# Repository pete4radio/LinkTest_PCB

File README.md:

# LinkTest_PCB
PCB for Dual LinkTesting

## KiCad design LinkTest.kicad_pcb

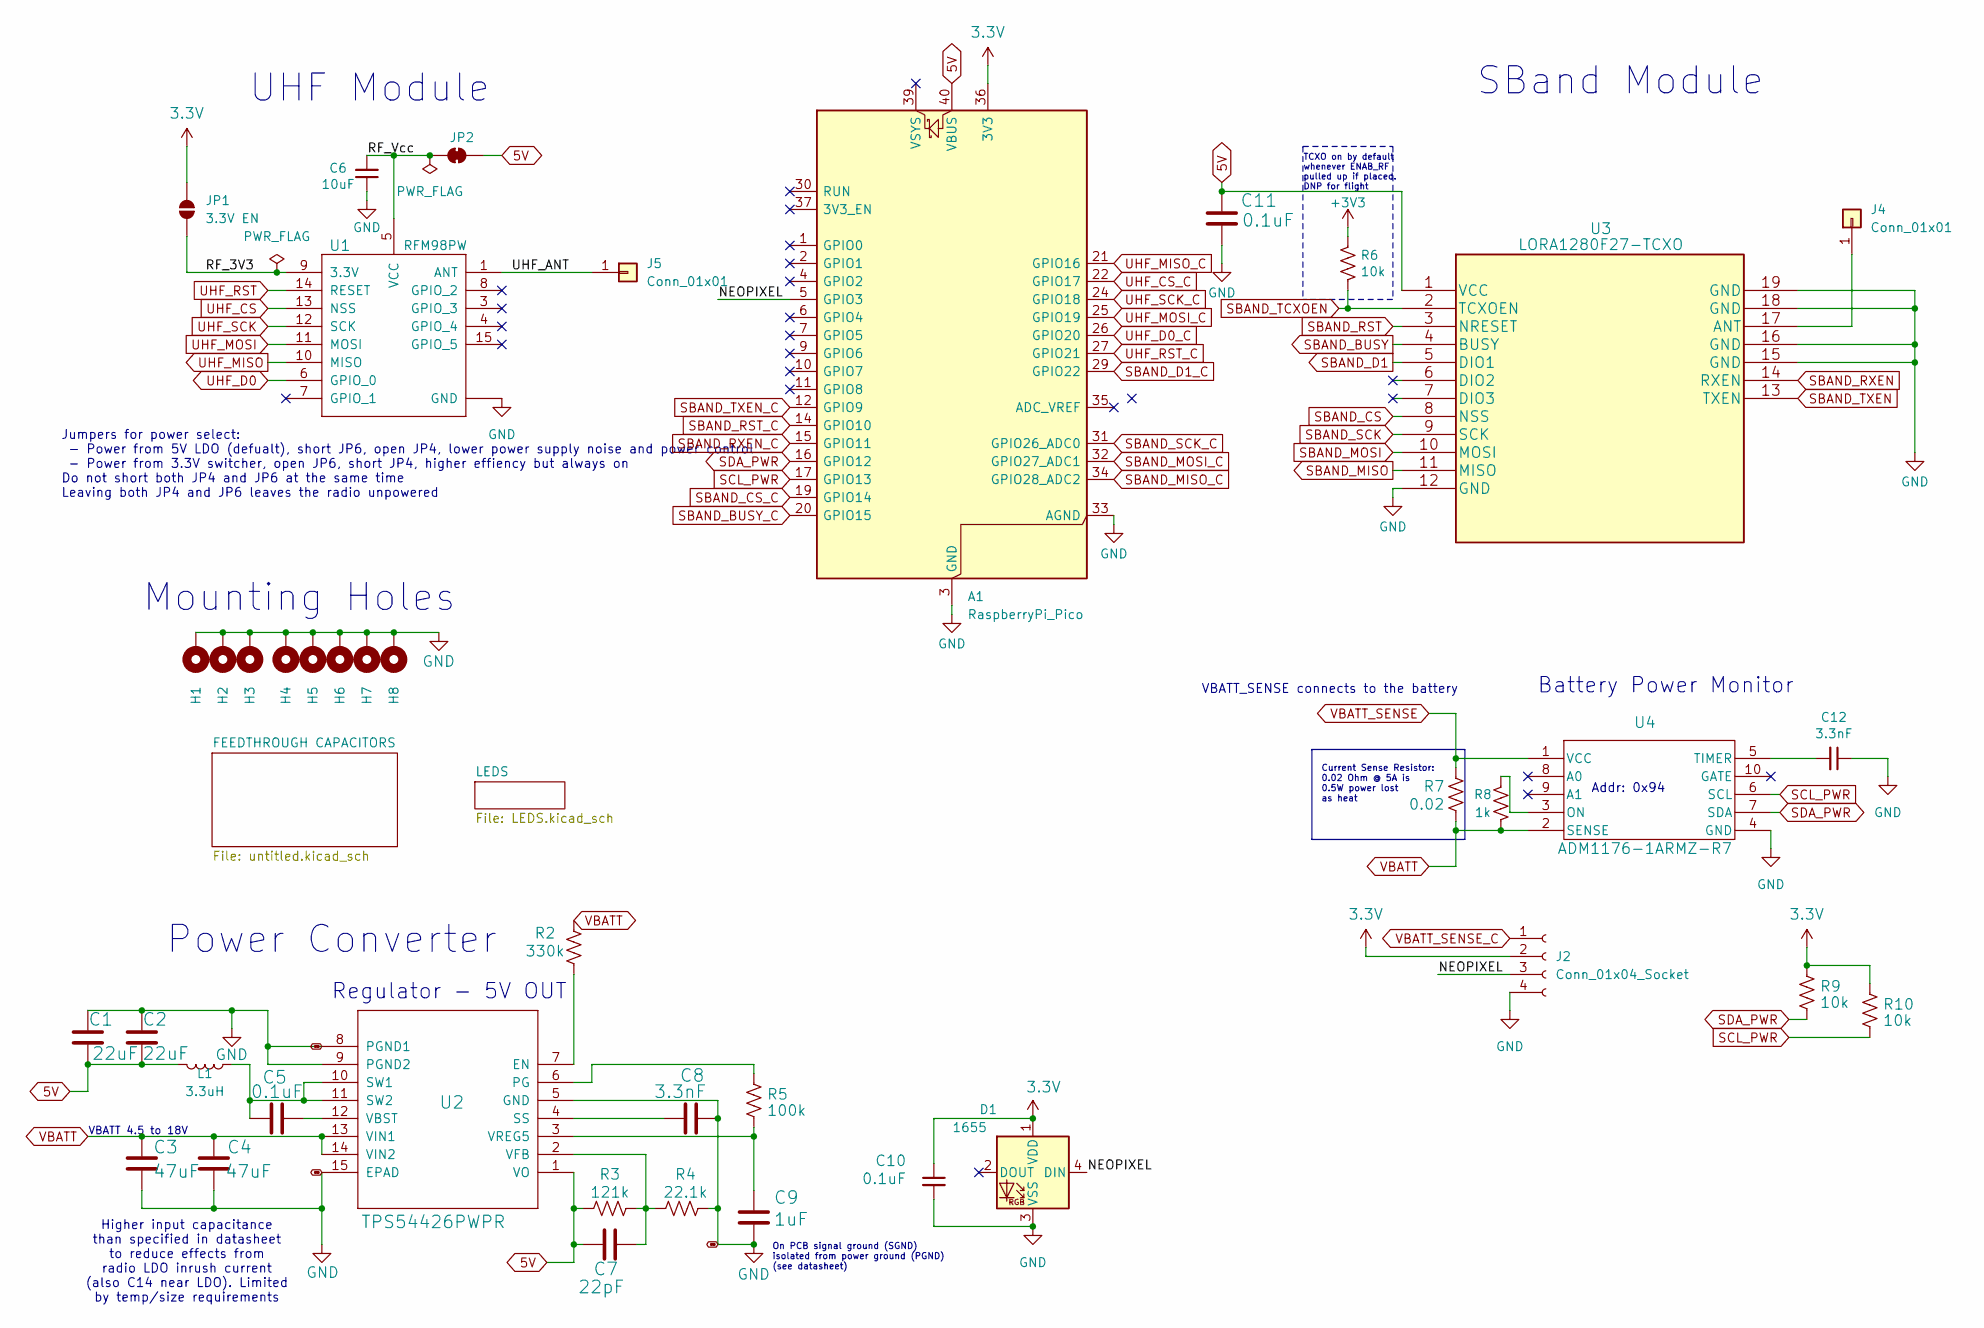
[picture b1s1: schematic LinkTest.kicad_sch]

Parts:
A1: RaspberryPi_Pico; RaspberryPi_Pico_SMD
C1, C2: 22uF; C_0603_1608Metric
C3, C4: 47uF; C_1210_3225Metric
C5, C10, C11: 0.1uF; C_0603_1608Metric
C6: 10uF; C_0603_1608Metric
C7: 22pF; C_0603_1608Metric
C8, C12: 3.3nF; C_0603_1608Metric
C9: 1uF; C_0603_1608Metric
D1: 1655; LED_WS2812B_PLCC4_5.0x5.0mm_P3.2mm; Manufacturer_Part_Number SK6812
H1, H2, H3, H4, H5, H6, H7, H8: MountingHole_Pad; MountingHole_2.7mm_M2.5_DIN965_Pad
J2: Conn_01x04_Socket; PinHeader_1x04_P2.54mm_Vertical
J4, J5: Conn_01x01; TestPoint_Keystone_5019_Miniature
JP1: 3.3V EN; SolderJumper-2_P1.3mm_Open_RoundedPad1.0x1.5mm
JP2: Jumper_3_Bridged12; SolderJumper-2_P1.3mm_Bridged_RoundedPad1.0x1.5mm
L1: 3.3uH; L_2141; Manufacturer_Part_Number HPC5040NF-3R3MTH
R2: 330k; R_0603_1608Metric
R3: 121k; R_0603_1608Metric
R4: 22.1k; R_0603_1608Metric
R5: 100k; R_0603_1608Metric
R6, R9, R10: 10k; R_0603_1608Metric
R7: 0.02; R_2512_6332Metric
R8: 1k; R_0603_1608Metric
U1: RFM98PW; Manufacturer_Part_Number RFM98PW
U2: TPS54426PWPR; PWP14_2P31X2P46-L; Manufacturer_Part_Number TPS54226PWPR
U3: LORA1280F27-TCXO; LORA128XF27
U4: ADM1176-1ARMZ-R7; Manufacturer_Part_Number ADM1176-1ARMZ-R7

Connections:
3.3V: A1.36 (3V3), C10.1, D1.1 (VDD), J2.2, JP1.2 (B), R9.1, R10.1
5V: A1.40 (VBUS), C1.2, C2.2, C7.1, C11.1, JP2.1 (A), L1.2, R3.2, U2.1 (VO), U3.1 (VCC)
+3V3: R6.1
/NEOPIXEL: A1.5 (GPIO3), D1.4 (DIN), J2.3
/RF_3V3: JP1.1 (A), U1.9 (3.3V)
/RF_Vcc: C6.2, JP2.2 (B), U1.5 (VCC)
/UHF_ANT: J5.1, U1.1 (ANT)
GND: A1.3 (GND), A1.8 (GND), A1.13 (GND), A1.18 (GND), A1.23 (GND), A1.28 (GND), A1.33 (AGND), A1.38 (GND), C1.1, C2.1, C3.2, C4.2, C6.1, C8.2, C9.2, C10.2, C11.2, C12.1, D1.3 (VSS), H1.1, H2.1, H3.1, H4.1, H5.1, H6.1, H7.1, H8.1, J2.4, R4.1, U1.2 (GND), U1.16 (GND), U1.17 (GND), U2.5 (GND), U2.8 (PGND1), U2.9 (PGND2), U2.15 (EPAD), U3.12 (GND), U3.15 (GND), U3.16 (GND), U3.18 (GND), U3.19 (GND), U4.4 (GND); also elsewhere on the board
unnamed: J4.1, U3.17 (ANT)
unnamed: R2.2, U2.7 (EN)
unnamed: R5.1, U2.6 (PG)
unnamed: C8.1, U2.4 (SS)
unnamed: C5.1, L1.1, U2.10 (SW1), U2.11 (SW2)
unnamed: C5.2, U2.12 (VBST)
unnamed: C7.2, R3.1, R4.2, U2.2 (VFB)
unnamed: C9.1, R5.2, U2.3 (VREG5)
unnamed: R8.2, U4.3 (ON)
unnamed: C12.2, U4.5 (TIMER)
SBAND_BUSY: U3.4 (BUSY); also elsewhere on the board
SBAND_BUSY_C: A1.20 (GPIO15); also elsewhere on the board
SBAND_CS: U3.8 (NSS); also elsewhere on the board
SBAND_CS_C: A1.19 (GPIO14); also elsewhere on the board
SBAND_D1: U3.5 (DIO1); also elsewhere on the board
SBAND_D1_C: A1.29 (GPIO22); also elsewhere on the board
SBAND_MISO: U3.11 (MISO); also elsewhere on the board
SBAND_MISO_C: A1.34 (GPIO28_ADC2); also elsewhere on the board
SBAND_MOSI: U3.10 (MOSI); also elsewhere on the board
SBAND_MOSI_C: A1.32 (GPIO27_ADC1); also elsewhere on the board
SBAND_RST: U3.3 (NRESET); also elsewhere on the board
SBAND_RST_C: A1.14 (GPIO10); also elsewhere on the board
SBAND_RXEN: U3.14 (RXEN); also elsewhere on the board
SBAND_RXEN_C: A1.15 (GPIO11); also elsewhere on the board
SBAND_SCK: U3.9 (SCK); also elsewhere on the board
SBAND_SCK_C: A1.31 (GPIO26_ADC0); also elsewhere on the board
SBAND_TCXOEN: R6.2, U3.2 (TCXOEN)
SBAND_TXEN: U3.13 (TXEN); also elsewhere on the board
SBAND_TXEN_C: A1.12 (GPIO9); also elsewhere on the board
SCL_PWR: A1.17 (GPIO13), R10.2, U4.6 (SCL)
SDA_PWR: A1.16 (GPIO12), R9.2, U4.7 (SDA)
UHF_CS: U1.13 (NSS); also elsewhere on the board
UHF_CS_C: A1.22 (GPIO17); also elsewhere on the board
UHF_D0: U1.6 (GPIO_0); also elsewhere on the board
UHF_D0_C: A1.26 (GPIO20); also elsewhere on the board
UHF_MISO: U1.10 (MISO); also elsewhere on the board
UHF_MISO_C: A1.21 (GPIO16); also elsewhere on the board
UHF_MOSI: U1.11 (MOSI); also elsewhere on the board
UHF_MOSI_C: A1.25 (GPIO19); also elsewhere on the board
UHF_RST: U1.14 (RESET); also elsewhere on the board
UHF_RST_C: A1.27 (GPIO21); also elsewhere on the board
UHF_SCK: U1.12 (SCK); also elsewhere on the board
UHF_SCK_C: A1.24 (GPIO18); also elsewhere on the board
VBATT: C3.1, C4.1, R2.1, R7.1, R8.1, U2.13 (VIN1), U2.14 (VIN2), U4.2 (SENSE); also elsewhere on the board
VBATT_SENSE: R7.2, U4.1 (VCC); also elsewhere on the board
VBATT_SENSE_C: J2.1; also elsewhere on the board

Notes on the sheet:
SBand Module
Addr: 0x94
Power Converter
VBATT 4.5 to 18V
Current Sense Resistor: 0.02 Ohm @ 5A is 0.5W power lost as heat
On PCB signal ground (SGND) isolated from power ground (PGND) (see datasheet)
UHF Module
VBATT_SENSE connects to the battery
Regulator - 5V OUT
Higher input capacitance than specified in datasheet to reduce effects from radio LDO inrush current (also C14 near LDO). Limited by temp/size requirements
Battery Power Monitor
Jumpers for power select: - Power from 5V LDO (defualt), short JP6, open JP4, lower power supply noise and power control - Power from 3.3V switcher, open JP6, short JP4, higher effiency but always on Do not short both JP4 and JP6 at the same time Leaving both JP4 and JP6 leaves the radio unpowered
Mounting Holes
TCXO on by default whenever ENAB_RF pulled up if placed. DNP for flight

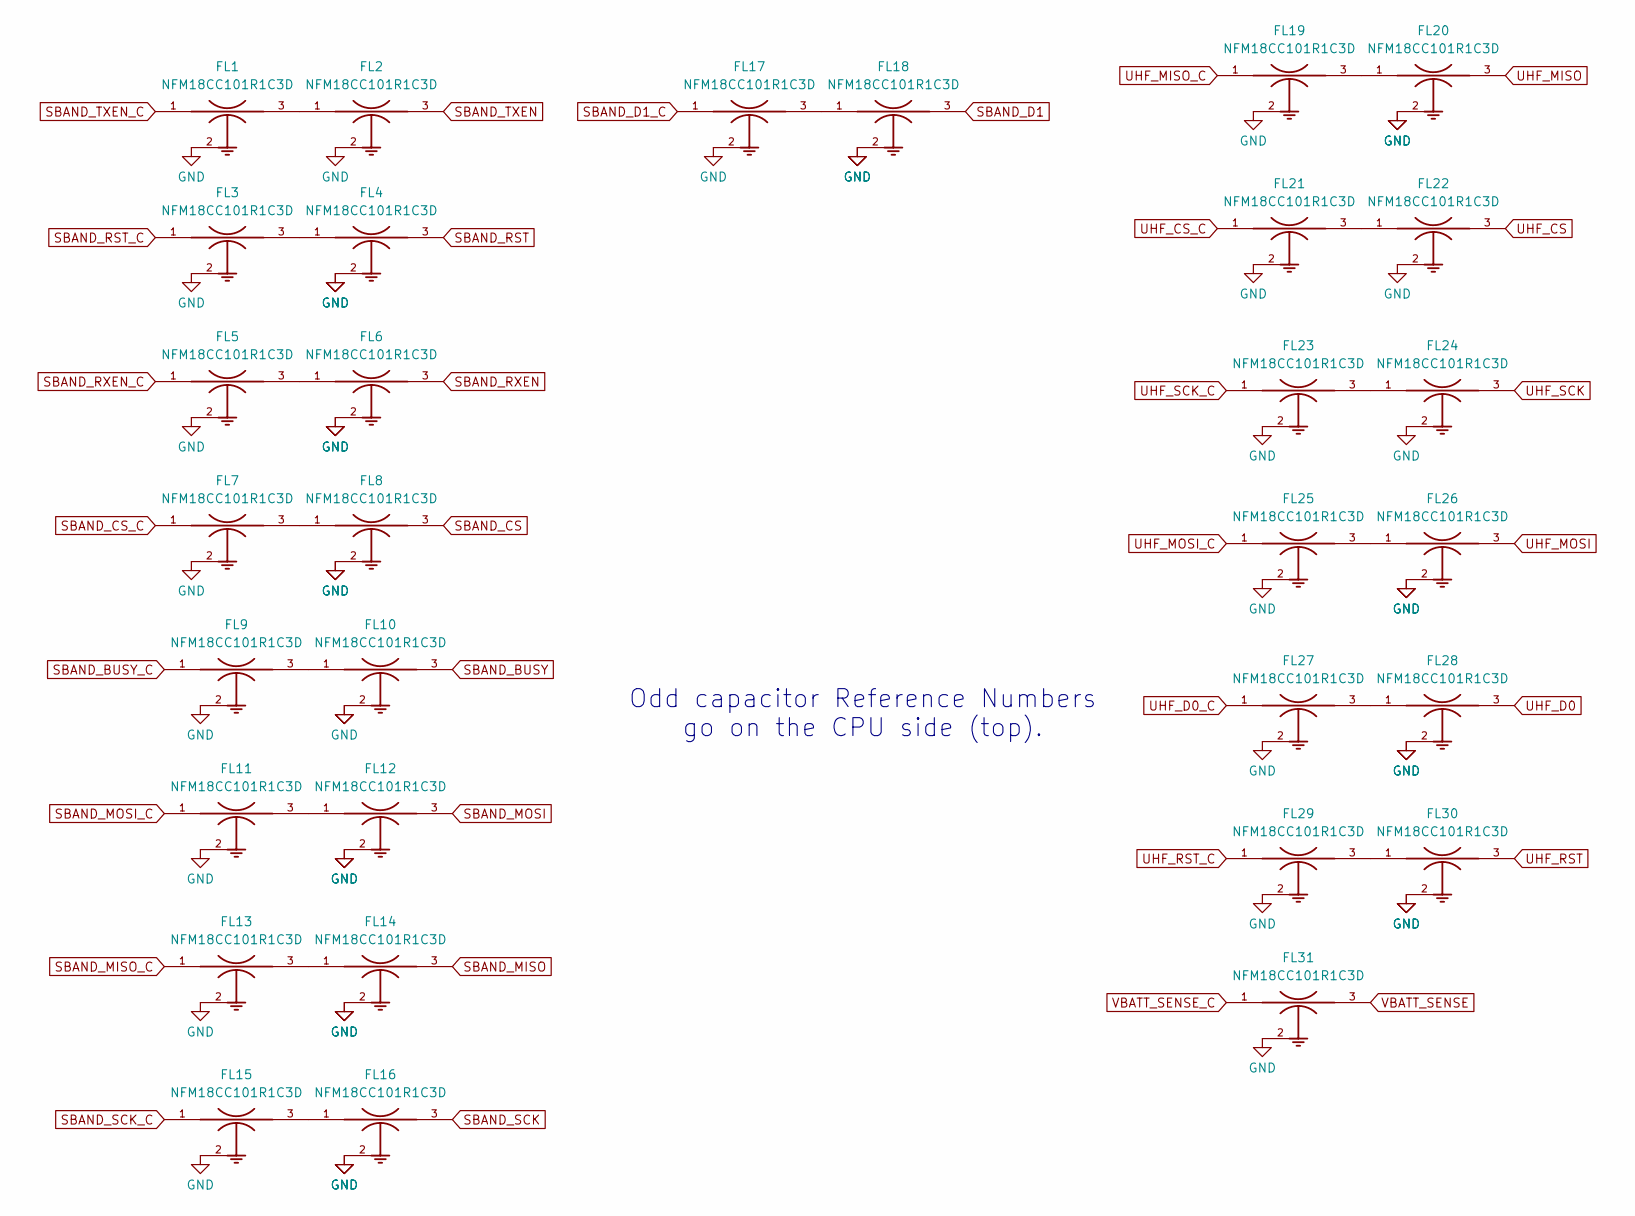
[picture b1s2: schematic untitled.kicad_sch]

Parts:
FL1, FL2, FL3, FL4, FL5, FL6, FL7, FL8, FL9, FL10, FL11, FL12, FL13, FL14, FL15, FL16, FL17, FL18, FL19, FL20, FL21, FL22, FL23, FL24, FL25, FL26, FL27, FL28, FL29, FL30, FL31: NFM18CC101R1C3D; FIL_NFM18CC101R1C3D; DigiKey_Part_Number 490-6961-1-ND

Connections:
GND: FL1.2, FL1.2_1, FL1.2_2, FL1.2_3, FL1.2_4, FL2.2, FL2.2_1, FL2.2_2, FL2.2_3, FL2.2_4, FL3.2, FL3.2_1, FL3.2_2, FL3.2_3, FL3.2_4, FL4.2, FL4.2_1, FL4.2_2, FL4.2_3, FL4.2_4, FL5.2, FL5.2_1, FL5.2_2, FL5.2_3, FL5.2_4, FL6.2, FL6.2_1, FL6.2_2, FL6.2_3, FL6.2_4, FL7.2, FL7.2_1, FL7.2_2, FL7.2_3, FL7.2_4, FL8.2, FL8.2_1, FL8.2_2, FL8.2_3, FL8.2_4, FL9.2, FL9.2_1, FL9.2_2, FL9.2_3, FL9.2_4, FL10.2, FL10.2_1, FL10.2_2, FL10.2_3, FL10.2_4, FL11.2, FL11.2_1, FL11.2_2, FL11.2_3, FL11.2_4, FL12.2, FL12.2_1, FL12.2_2, FL12.2_3, FL12.2_4, FL13.2, FL13.2_1, FL13.2_2, FL13.2_3, FL13.2_4, FL14.2, FL14.2_1, FL14.2_2, FL14.2_3, FL14.2_4, FL15.2, FL15.2_1, FL15.2_2, FL15.2_3, FL15.2_4, FL16.2, FL16.2_1, FL16.2_2, FL16.2_3, FL16.2_4, FL17.2, FL17.2_1, FL17.2_2, FL17.2_3, FL17.2_4, FL18.2, FL18.2_1, FL18.2_2, FL18.2_3, FL18.2_4, FL19.2, FL19.2_1, FL19.2_2, FL19.2_3, FL19.2_4, FL20.2, FL20.2_1, FL20.2_2, FL20.2_3, FL20.2_4, FL21.2, FL21.2_1, FL21.2_2, FL21.2_3, FL21.2_4, FL22.2, FL22.2_1, FL22.2_2, FL22.2_3, FL22.2_4, FL23.2, FL23.2_1, FL23.2_2, FL23.2_3, FL23.2_4, FL24.2, FL24.2_1, FL24.2_2, FL24.2_3, FL24.2_4, FL25.2, FL25.2_1, FL25.2_2, FL25.2_3, FL25.2_4, FL26.2, FL26.2_1, FL26.2_2, FL26.2_3, FL26.2_4, FL27.2, FL27.2_1, FL27.2_2, FL27.2_3, FL27.2_4, FL28.2, FL28.2_1, FL28.2_2, FL28.2_3, FL28.2_4, FL29.2, FL29.2_1, FL29.2_2, FL29.2_3, FL29.2_4, FL30.2, FL30.2_1, FL30.2_2, FL30.2_3, FL30.2_4, FL31.2, FL31.2_1, FL31.2_2, FL31.2_3, FL31.2_4; also elsewhere on the board
unnamed: FL1.3, FL2.1
unnamed: FL3.3, FL4.1
unnamed: FL5.3, FL6.1
unnamed: FL7.3, FL8.1
unnamed: FL9.3, FL10.1
unnamed: FL11.3, FL12.1
unnamed: FL13.3, FL14.1
unnamed: FL15.3, FL16.1
unnamed: FL17.3, FL18.1
unnamed: FL19.3, FL20.1
unnamed: FL21.3, FL22.1
unnamed: FL23.3, FL24.1
unnamed: FL25.3, FL26.1
unnamed: FL27.3, FL28.1
unnamed: FL29.3, FL30.1
SBAND_BUSY: FL10.3; also elsewhere on the board
SBAND_BUSY_C: FL9.1; also elsewhere on the board
SBAND_CS: FL8.3; also elsewhere on the board
SBAND_CS_C: FL7.1; also elsewhere on the board
SBAND_D1: FL18.3; also elsewhere on the board
SBAND_D1_C: FL17.1; also elsewhere on the board
SBAND_MISO: FL14.3; also elsewhere on the board
SBAND_MISO_C: FL13.1; also elsewhere on the board
SBAND_MOSI: FL12.3; also elsewhere on the board
SBAND_MOSI_C: FL11.1; also elsewhere on the board
SBAND_RST: FL4.3; also elsewhere on the board
SBAND_RST_C: FL3.1; also elsewhere on the board
SBAND_RXEN: FL6.3; also elsewhere on the board
SBAND_RXEN_C: FL5.1; also elsewhere on the board
SBAND_SCK: FL16.3; also elsewhere on the board
SBAND_SCK_C: FL15.1; also elsewhere on the board
SBAND_TXEN: FL2.3; also elsewhere on the board
SBAND_TXEN_C: FL1.1; also elsewhere on the board
UHF_CS: FL22.3; also elsewhere on the board
UHF_CS_C: FL21.1; also elsewhere on the board
UHF_D0: FL28.3; also elsewhere on the board
UHF_D0_C: FL27.1; also elsewhere on the board
UHF_MISO: FL20.3; also elsewhere on the board
UHF_MISO_C: FL19.1; also elsewhere on the board
UHF_MOSI: FL26.3; also elsewhere on the board
UHF_MOSI_C: FL25.1; also elsewhere on the board
UHF_RST: FL30.3; also elsewhere on the board
UHF_RST_C: FL29.1; also elsewhere on the board
UHF_SCK: FL24.3; also elsewhere on the board
UHF_SCK_C: FL23.1; also elsewhere on the board
VBATT_SENSE: FL31.3; also elsewhere on the board
VBATT_SENSE_C: FL31.1; also elsewhere on the board

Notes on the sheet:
Odd capacitor Reference Numbers go on the CPU side (top).

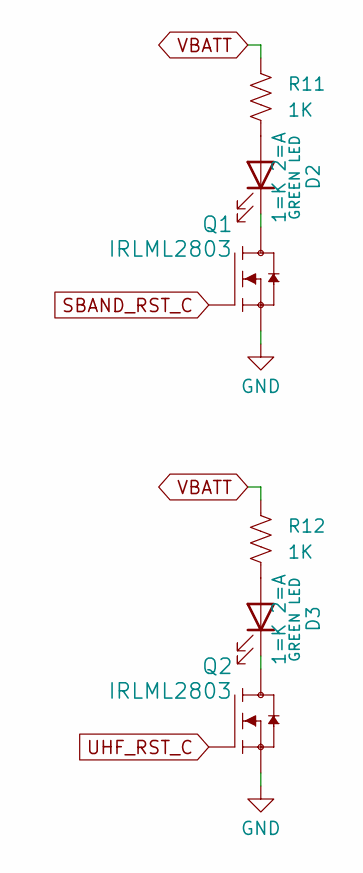
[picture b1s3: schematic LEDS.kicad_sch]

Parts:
D2, D3: GREEN LED; LED_0603_1608Metric; Manufacturer_Part_Number LTST-C190KGKT
Q1, Q2: IRLML2803; SOT-23; Manufacturer_Part_Number MMBT2222AT
R11, R12: 1K; R_0603_1608Metric

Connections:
GND: Q1.2 (S), Q2.2 (S); also elsewhere on the board
unnamed: D2.2 (A), R11.2
unnamed: D2.1 (K), Q1.3 (D)
unnamed: D3.2 (A), R12.2
unnamed: D3.1 (K), Q2.3 (D)
SBAND_RST_C: Q1.1 (G); also elsewhere on the board
UHF_RST_C: Q2.1 (G); also elsewhere on the board
VBATT: R11.1, R12.1; also elsewhere on the board

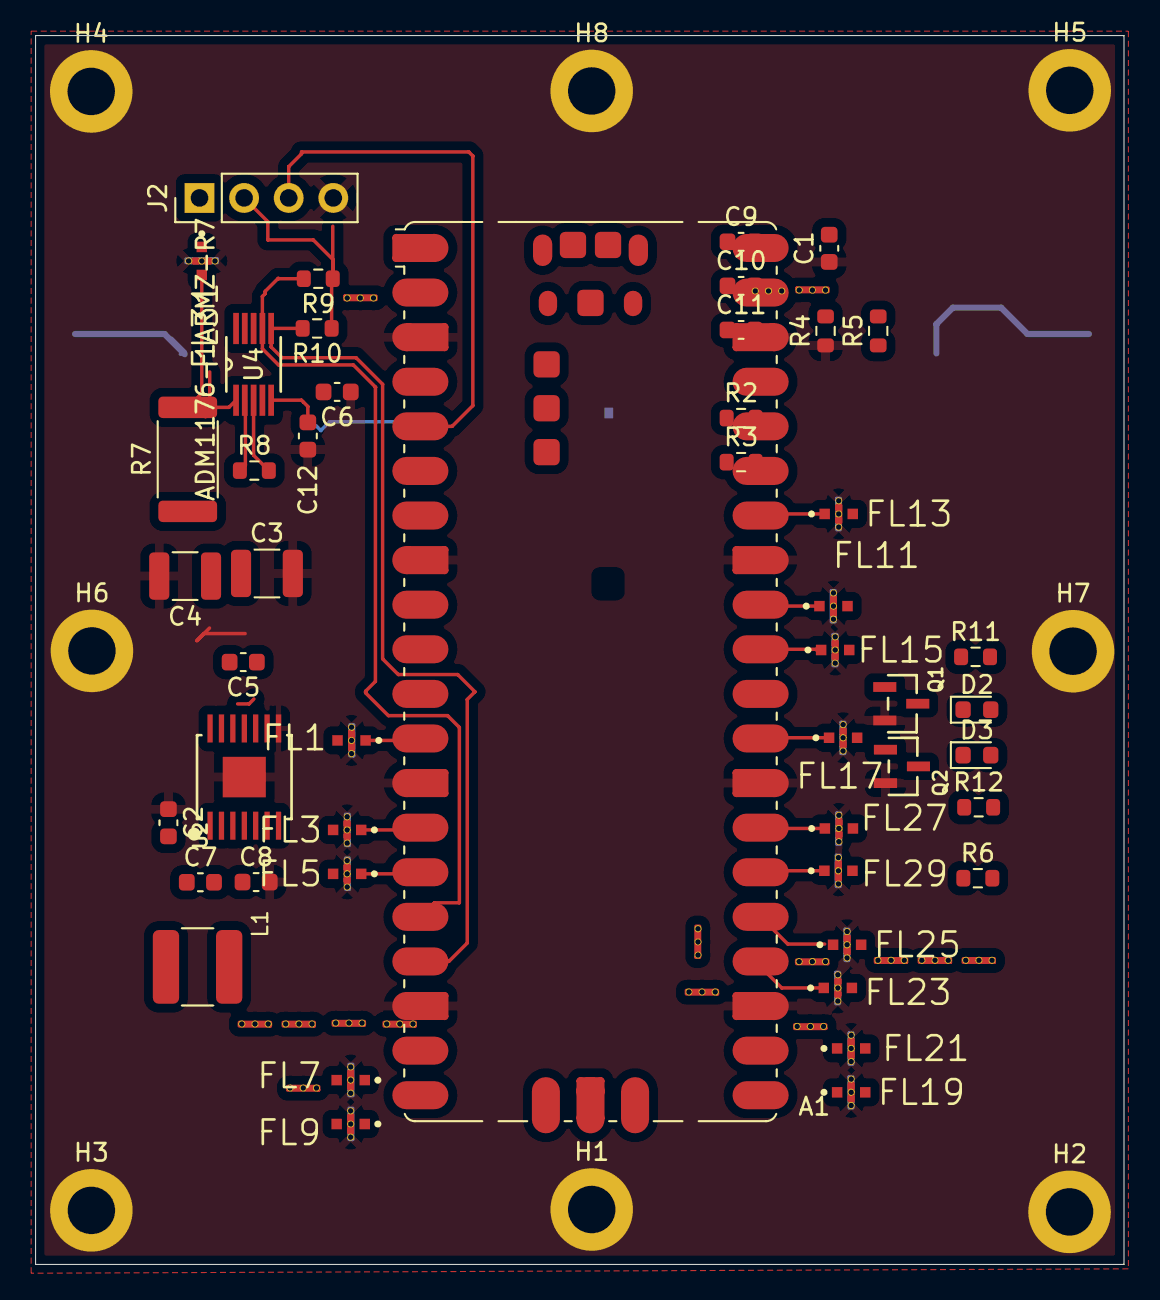
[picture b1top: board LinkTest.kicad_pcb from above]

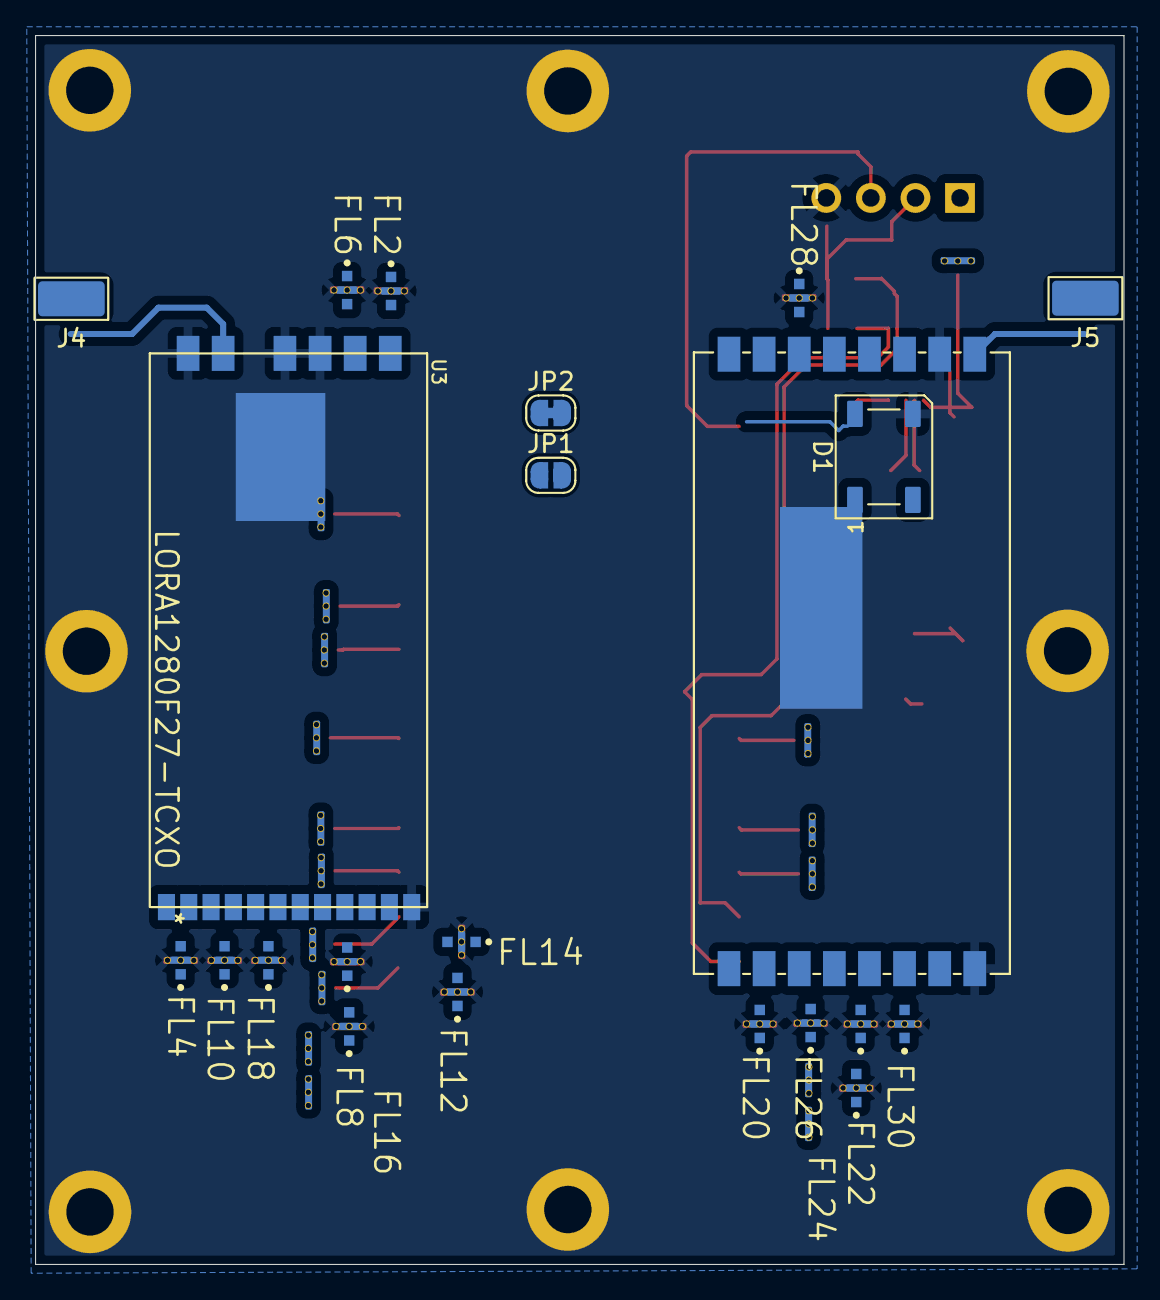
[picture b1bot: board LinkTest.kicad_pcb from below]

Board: 4 copper layers, 62.0 x 70.0 mm, 78 parts (22 on the bottom side), 72 nets.

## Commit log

2026-01-01 Initial upload
2026-01-02 Feedthrough symbol and footprint
2026-01-02 started placement of feed through
2026-01-02 SMD Pads on pico
2026-01-02 remove CS pullup
2026-01-02 Antenna connection, gnd planes, in process of getting feedthrough caps to connect to ground
2026-01-03 50 ohm netclass
2026-01-04 Power Monitor and 5V reg laid out; mechanicals on USER1 layer

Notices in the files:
parts and their libraries:
Copyright 2016 Accelerated Designs. All rights reserved.
